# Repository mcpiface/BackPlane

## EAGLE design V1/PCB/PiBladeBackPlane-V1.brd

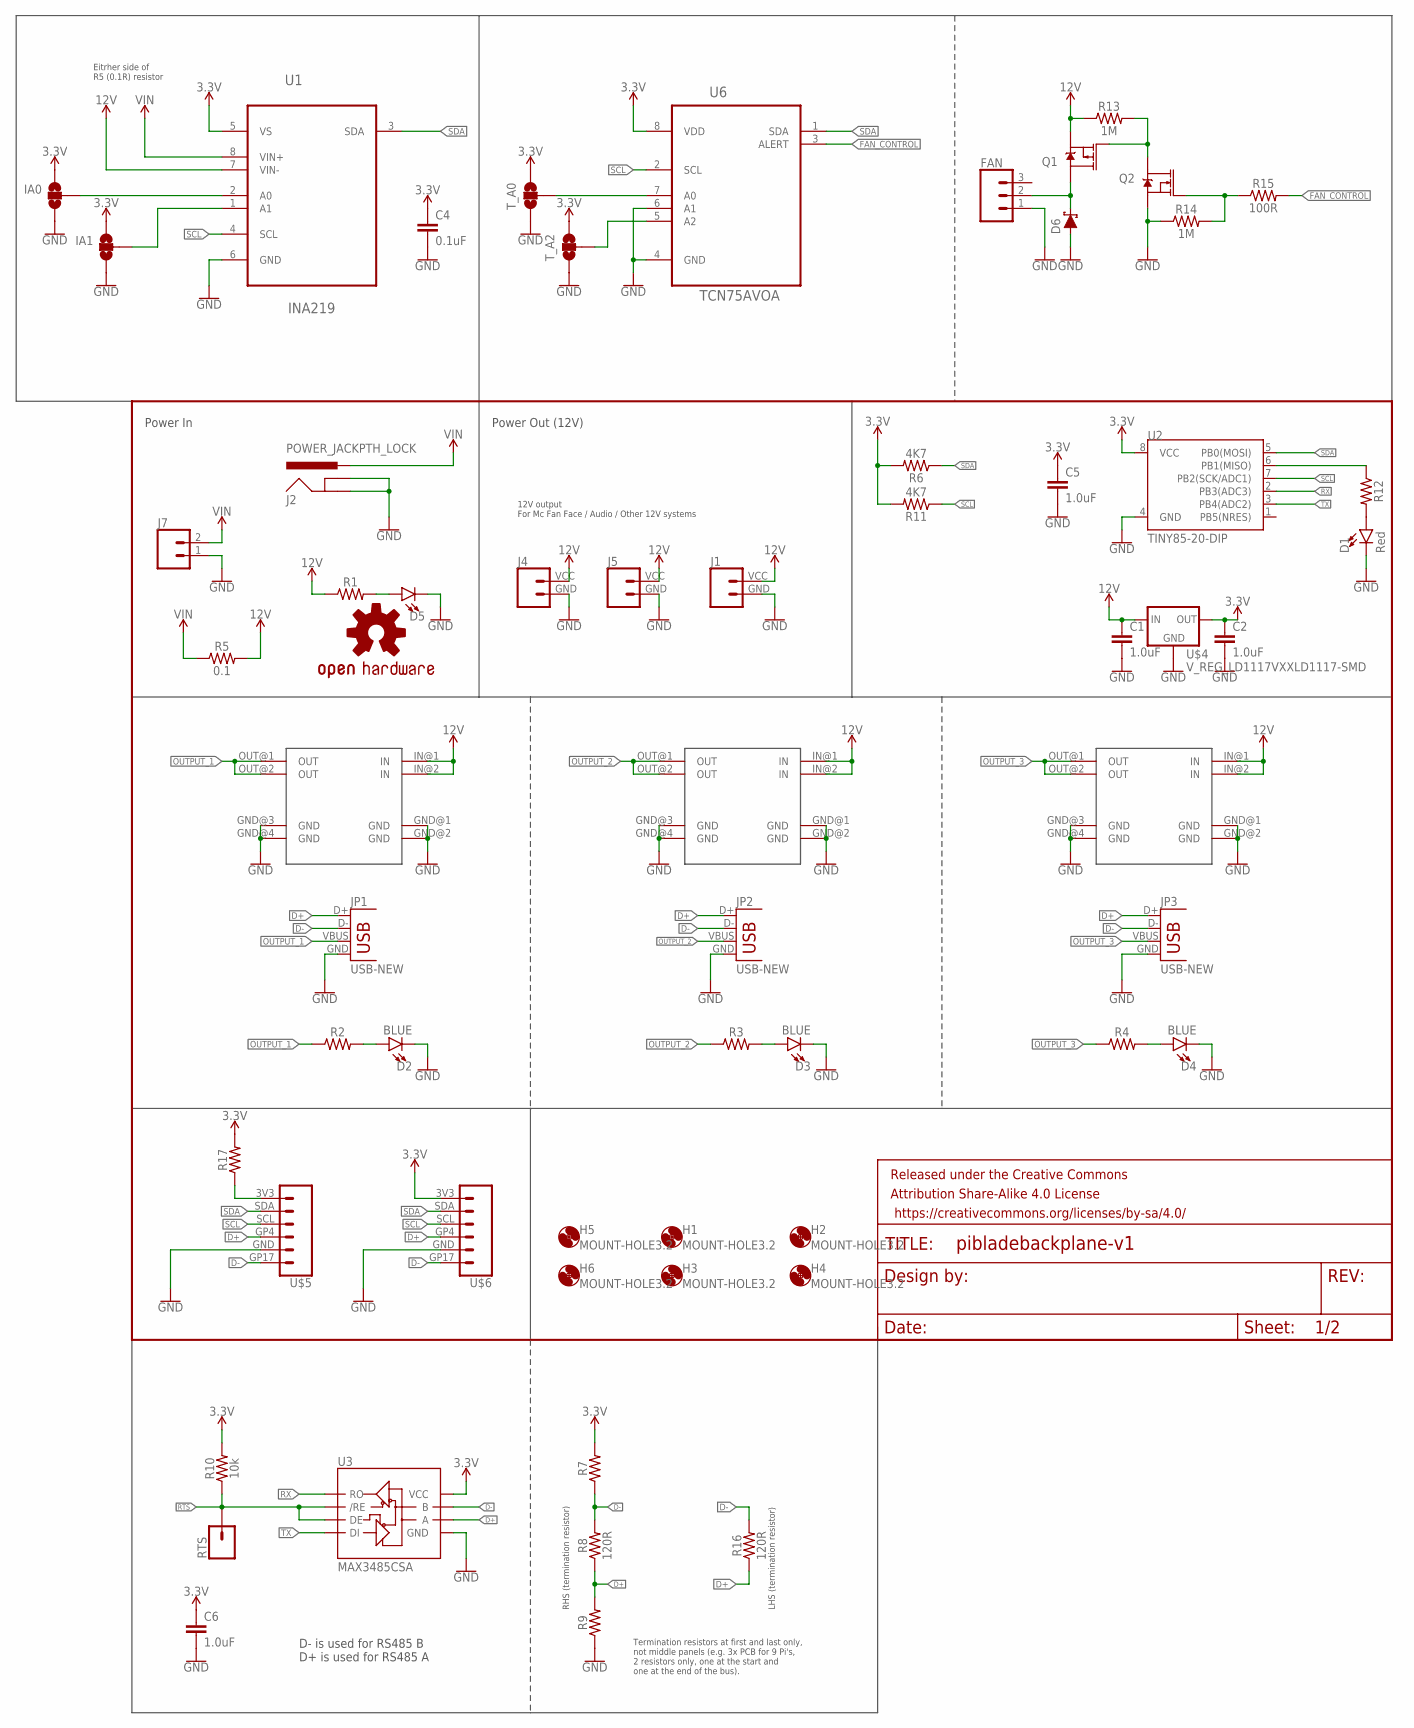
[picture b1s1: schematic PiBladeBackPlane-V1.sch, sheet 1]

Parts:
C1, C2, C5, C6: 1.0uF; 0805
C4: 0.1uF; 0805
D1: Red; LED-1206
D2, D3, D4: BLUE; LED-1206
D5: LED1206-BOTTOM; LED-1206-BOTTOM
D6: 1A/23V/620mV; SOD-323
FAN: CONN_03POLAR; MOLEX-1X3
FRAME1: FRAME-LETTER; CREATIVE_COMMONS
H1, H2, H3, H4, H5, H6: MOUNT-HOLE3.2; 3,2
IA0, IA1: JUMPER-SMT_3_NO_NO_SILK; SMT-JUMPER_3_0-NO_TRACE_NO-SILK
J1, J4, J5: CONN_02JST-2-PH-VERT; JST-2-SMD-VERT
J2: POWER_JACKPTH_LOCK; POWER_JACK_PTH_LOCK
J7: CONN_025MM; SCREWTERMINAL-5MM-2
JP1, JP2, JP3: USB-NEW; USB-A-VERTICAL
LOGO1: OSHW-LOGOM; OSHW-LOGO-M
Q1: 4.3A/20V/54mΩ; SOT23-3
Q2: 310mA/60V/1.6Ω; SOT323
R1, R2, R3, R4, R7, R9, R12: 0805
R5: 0.1; 1210
R6, R11: 4K7; 0805
R8, R16: 120R; 0805
R10: 10k; 0805
R13, R14: 1M; 0805
R15: 100R; 0805
R17: 1206
RTS: CONN_01; 1X01
T_A0, T_A2: JUMPER-SMT_3_NO_NO_SILK; SMT-JUMPER_3_0-NO_TRACE_NO-SILK
U1: INA219; SO08
U2: TINY85-20-DIP; DIP08_MCU
U3: MAX3485CSA; SO08
U6: TCN75AVOA; SOIC127P600X175-8N
U$1, U$2, U$3: MINI-BUCK-MODULE-3A
U$4: V_REG_LD1117VXXLD1117-SMD; SOT223
U$5, U$6: MC_PI_FACE_CONNECTORS_I2CTOP; JST-6-SH-1.0MM-TOP

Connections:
3.3V: C2.1, C4.1, C5.1, C6.1, IA0.1, IA1.1, R6.2, R7.2, R10.2, R11.2, R17.2, T_A0.1, T_A2.1, U1.5 (VS), U2.8 (VCC), U3.8 (VCC), U6.8 (VDD), U$4.2 (OUT), U$6.3V3
12V: C1.1, J1.VCC (2), J4.VCC (2), J5.VCC (2), Q1.2 (S), R1.1, R5.2, R13.1, U1.7 (VIN-), U$1.IN@1 (IN), U$1.IN@2 (IN), U$2.IN@1 (IN), U$2.IN@2 (IN), U$3.IN@1 (IN), U$3.IN@2 (IN), U$4.3 (IN)
A0: IA0.2, U1.2 (A0)
A1: IA1.2, U1.1 (A1)
D+: JP1.D+, JP2.D+, JP3.D+, R8.1, R9.2, R16.1, U3.6 (A), U$5.GP4, U$6.GP4
D-: JP1.D-, JP2.D-, JP3.D-, R7.1, R8.2, R16.2, U3.7 (B), U$5.GP17, U$6.GP17
FAN_CONTROL: R15.2, U6.3 (ALERT)
GND: C1.2, C2.2, C4.2, C5.2, C6.2, D1.C, D2.C, D3.C, D4.C, D5.C, D6.A, FAN.1, IA0.3, IA1.3, J1.GND (1), J2.GND, J2.GNDBREAK, J4.GND (1), J5.GND (1), J7.1, JP1.GND, JP2.GND, JP3.GND, Q2.2 (S), R9.1, R14.1, T_A0.3, T_A2.3, U1.6 (GND), U2.4 (GND), U3.5 (GND), U6.4 (GND), U6.6 (A1), U$1.GND@1 (GND), U$1.GND@2 (GND), U$1.GND@3 (GND), U$1.GND@4 (GND), U$2.GND@1 (GND), U$2.GND@2 (GND), U$2.GND@3 (GND), U$2.GND@4 (GND), U$3.GND@1 (GND), U$3.GND@2 (GND), U$3.GND@3 (GND), U$3.GND@4 (GND), U$4.1 (GND), U$5.GND, U$6.GND
unnamed: D5.A, R1.2
unnamed: D4.A, R4.2
unnamed: D2.A, R2.2
unnamed: D1.A, R12.2
unnamed: D3.A, R3.2
unnamed: R12.1, U2.6 (PB1(MISO))
unnamed: Q1.1 (G), Q2.3 (D), R13.2
unnamed: D6.C, FAN.2, Q1.3 (D)
unnamed: T_A0.2, U6.7 (A0)
unnamed: T_A2.2, U6.5 (A2)
unnamed: Q2.1 (G), R14.2, R15.1
unnamed: R17.1, U$5.3V3
OUTPUT_1: JP1.VBUS, R2.1, U$1.OUT@1 (OUT), U$1.OUT@2 (OUT)
OUTPUT_2: JP2.VBUS, R3.1, U$2.OUT@1 (OUT), U$2.OUT@2 (OUT)
OUTPUT_3: JP3.VBUS, R4.1, U$3.OUT@1 (OUT), U$3.OUT@2 (OUT)
RTS: R10.1, RTS.1, U3.2 (/RE), U3.3 (DE)
RX: U2.2 (PB3(ADC3)), U3.1 (RO)
SCL: R11.1, U1.4 (SCL), U2.7 (PB2(SCK/ADC1)), U6.2 (SCL), U$5.SCL, U$6.SCL
SDA: R6.1, U1.3 (SDA), U2.5 (PB0(MOSI)), U6.1 (SDA), U$5.SDA, U$6.SDA
TX: U2.3 (PB4(ADC2)), U3.4 (DI)
VIN: J2.PWR, J7.2, R5.1, U1.8 (VIN+)

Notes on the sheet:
12V output For Mc Fan Face / Audio / Other 12V systems
Power In
Power Out (12V)
LHS (termination resistor)
RHS (termination resistor)
Termination resistors at first and last only, not middle panels (e.g. 3x PCB for 9 Pi's, 2 resistors only, one at the start and one at the end of the bus).
Eitrher side of R5 (0.1R) resistor
D- is used for RS485 B D+ is used for RS485 A

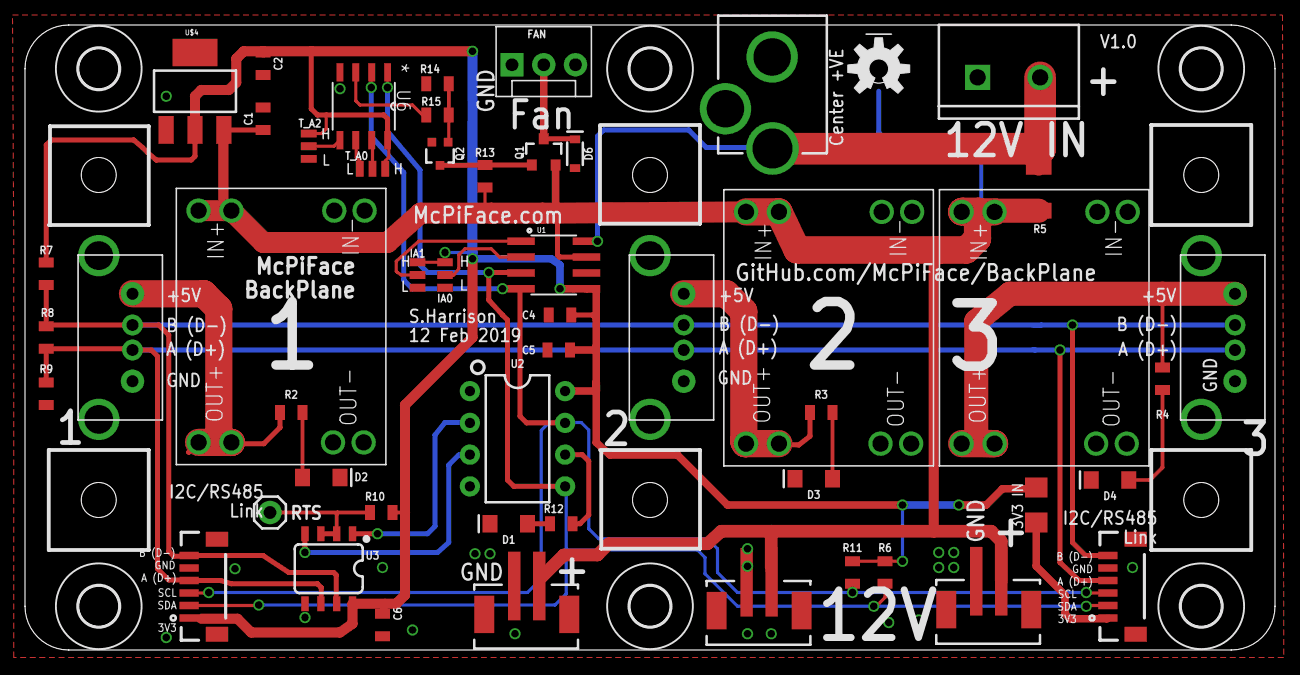
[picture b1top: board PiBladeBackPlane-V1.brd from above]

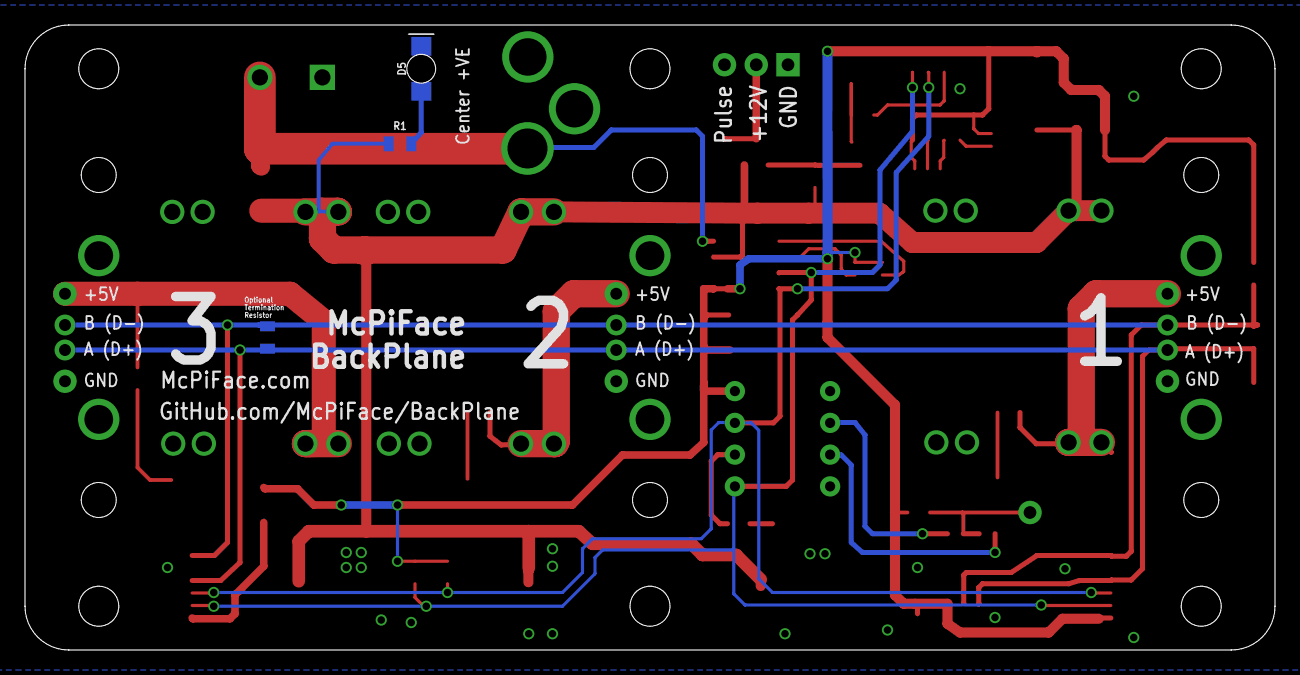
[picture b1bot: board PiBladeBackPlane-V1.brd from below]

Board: 2 copper layers, 100.0 x 50.0 mm, 62 parts (6 on the bottom side), 29 nets.

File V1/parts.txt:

Partlist

Exported from PiBladeBackPlane-V1.brd at 15/02/2019 19:36

EAGLE Version 7.4.0 Copyright (c) 1988-2015 CadSoft

Assembly variant: 

Part     Value                        Package                         Library               Position (inch)       Orientation

C1       1.0uF                        0805                            SparkFun-Capacitors   (0.74990157 1.67322835) R90
C2       1.0uF                        0805                            SparkFun-Capacitors   (0.74990157 1.84645669) R270
C4       0.1uF                        0805                            SparkFun-Capacitors   (1.68503937 1.05511811) R180
C5       1.0uF                        0805                            SparkFun-Capacitors   (1.68110236 0.94488189) R180
C6       1.0uF                        0805                            SparkFun-Capacitors   (1.12598425 0.07874016) R270
D1       Red                          LED-1206                        SparkFun-LED          (1.52362205 0.3976378) R180
D2       BLUE                         LED-1206                        SparkFun-LED          (0.93307087 0.54330709) R0
D3       BLUE                         LED-1206                        SparkFun-LED          (2.48425197 0.53937008) R180
D4       BLUE                         LED-1206                        SparkFun-LED          (3.41732283 0.53543307) R180
D5                                    LED-1206-BOTTOM                 SparkFun-LED          (2.68897638 1.83070866) MR90
D6       1A/23V/620mV                 SOD-323                         SparkFun-DiscreteSemi (1.73228346 1.56299213) R270
FAN                                   MOLEX-1X3                       SparkFun-Connectors   (1.53385827 1.84330709) R0
IA0      JUMPER-SMT_3_NO_NO_SILK      SMT-JUMPER_3_0-NO_TRACE_NO-SILK SparkFun-Jumpers      (1.32283465 1.18110236) R270
IA1      JUMPER-SMT_3_NO_NO_SILK      SMT-JUMPER_3_0-NO_TRACE_NO-SILK SparkFun-Jumpers      (1.23622047 1.18110236) R270
J1                                    JST-2-SMD-VERT                  ThingySticks          (3.03543307 0.13779528) R180
J2       POWER_JACKPTH_LOCK           POWER_JACK_PTH_LOCK             SparkFun-Connectors   (2.35433071 2.12598425) R180
J4                                    JST-2-SMD-VERT                  ThingySticks          (1.58031496 0.12283465) R180
J5                                    JST-2-SMD-VERT                  ThingySticks          (2.31220472 0.13464567) R180
J7                                    SCREWTERMINAL-5MM-2             SparkFun-Connectors   (3.0003937 1.80354331) R0
JP1      USB-NEW                      USB-A-VERTICAL                  Tinamous              (0.23228346 0.98425197) MR180
JP2      USB-NEW                      USB-A-VERTICAL                  Tinamous              (1.96850394 0.98425197) MR180
JP3      USB-NEW                      USB-A-VERTICAL                  Tinamous              (3.70472441 0.98425197) MR180
Q1       4.3A/20V/54m?                SOT23-3                         SparkFun-DiscreteSemi (1.63385827 1.56692913) R0
Q2       310mA/60V/1.6?               SOT323                          SparkFun-DiscreteSemi (1.30708661 1.56299213) R180
R1                                    0805                            SparkFun-Resistors    (2.75590551 1.59448819) MR0
R2                                    0805                            SparkFun-Resistors    (0.83858268 0.7480315) R0
R3                                    0805                            SparkFun-Resistors    (2.50787402 0.7480315) R0
R4                                    0805                            SparkFun-Resistors    (3.58267717 0.85433071) R270
R5       0.1                          1210                            SparkFun-Resistors    (3.19291339 1.45275591) R270
R6       4K7                          0805                            SparkFun-Resistors    (2.70866142 0.24409449) R90
R7                                    0805                            SparkFun-Resistors    (0.06692913 1.18503937) R90
R8       120R                         0805                            SparkFun-Resistors    (0.06692913 0.98425197) R90
R9                                    0805                            SparkFun-Resistors    (0.06692913 0.80708661) R90
R10      10k                          0805                            SparkFun-Resistors    (1.12204724 0.43307087) R0
R11      4K7                          0805                            SparkFun-Resistors    (2.60629921 0.24409449) R90
R12                                   0805                            SparkFun-Resistors    (1.68897638 0.3976378) R180
R13      1M                           0805                            SparkFun-Resistors    (1.4488189 1.49212598) R90
R14      1M                           0805                            SparkFun-Resistors    (1.2992126 1.78346457) R0
R15      100R                         0805                            SparkFun-Resistors    (1.2992126 1.68503937) R180
R16      120R                         0805                            SparkFun-Resistors    (3.17322835 0.98425197) MR90
R17                                   1206                            SparkFun-Resistors    (3.18503937 0.45669291) R90
RTS                                   1X01                            SparkFun-Connectors   (0.77165354 0.43307087) R0
T_A0     JUMPER-SMT_3_NO_NO_SILK      SMT-JUMPER_3_0-NO_TRACE_NO-SILK SparkFun-Jumpers      (1.09448819 1.51574803) R180
T_A2     JUMPER-SMT_3_NO_NO_SILK      SMT-JUMPER_3_0-NO_TRACE_NO-SILK SparkFun-Jumpers      (0.89370079 1.58661417) R270
U$1      MINI-BUCK-MODULE-3A          MINI-BUCK-MODULE-3A             Tinamous              (1.13661417 0.58385827) R90
U$2      MINI-BUCK-MODULE-3A          MINI-BUCK-MODULE-3A             Tinamous              (2.86102362 0.57992126) R90
U$3      MINI-BUCK-MODULE-3A          MINI-BUCK-MODULE-3A             Tinamous              (3.54015748 0.57992126) R90
U$4      V_REG_LD1117VXXLD1117-SMD    SOT223                          SparkFun-IC-Power     (0.53543307 1.75984252) R0
U$5      MC_PI_FACE_CONNECTORS_I2CTOP JST-6-SH-1.0MM-TOP              McPiFace              (3.46062992 0.2007874) R90
U$6      MC_PI_FACE_CONNECTORS_I2CTOP JST-6-SH-1.0MM-TOP              McPiFace              (0.56692913 0.2007874) R90
U1       INA219                       SO08                            INA219AIDCNR          (1.66535433 1.21259843) R270
U2       TINY85-20-DIP                DIP08_MCU                       SparkFun-Retired      (1.5511811 0.66535433) R270
U3        MAX3485CSA                  SO08                            SparkFun-IC-Comms     (0.95669291 0.25590551) R180
U6       TCN75AVOA                    SOIC127P600X175-8N              Microchip-TCN75AVOA   (1.06692913 1.71259843) R270

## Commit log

2019-02-15 Initial version as sent to DirtyPCBs.com

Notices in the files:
parts and their libraries:
SparkFun-Connectors: Licensing: Creative Commons ShareAlike 4.0 International - https://creativecommons.org/licenses/by-sa/4.0
SparkFun-Aesthetics: Released under the Creative Commons Attribution Share-Alike 4.0 License
SparkFun-Aesthetics: https://creativecommons.org/licenses/by-sa/4.0
